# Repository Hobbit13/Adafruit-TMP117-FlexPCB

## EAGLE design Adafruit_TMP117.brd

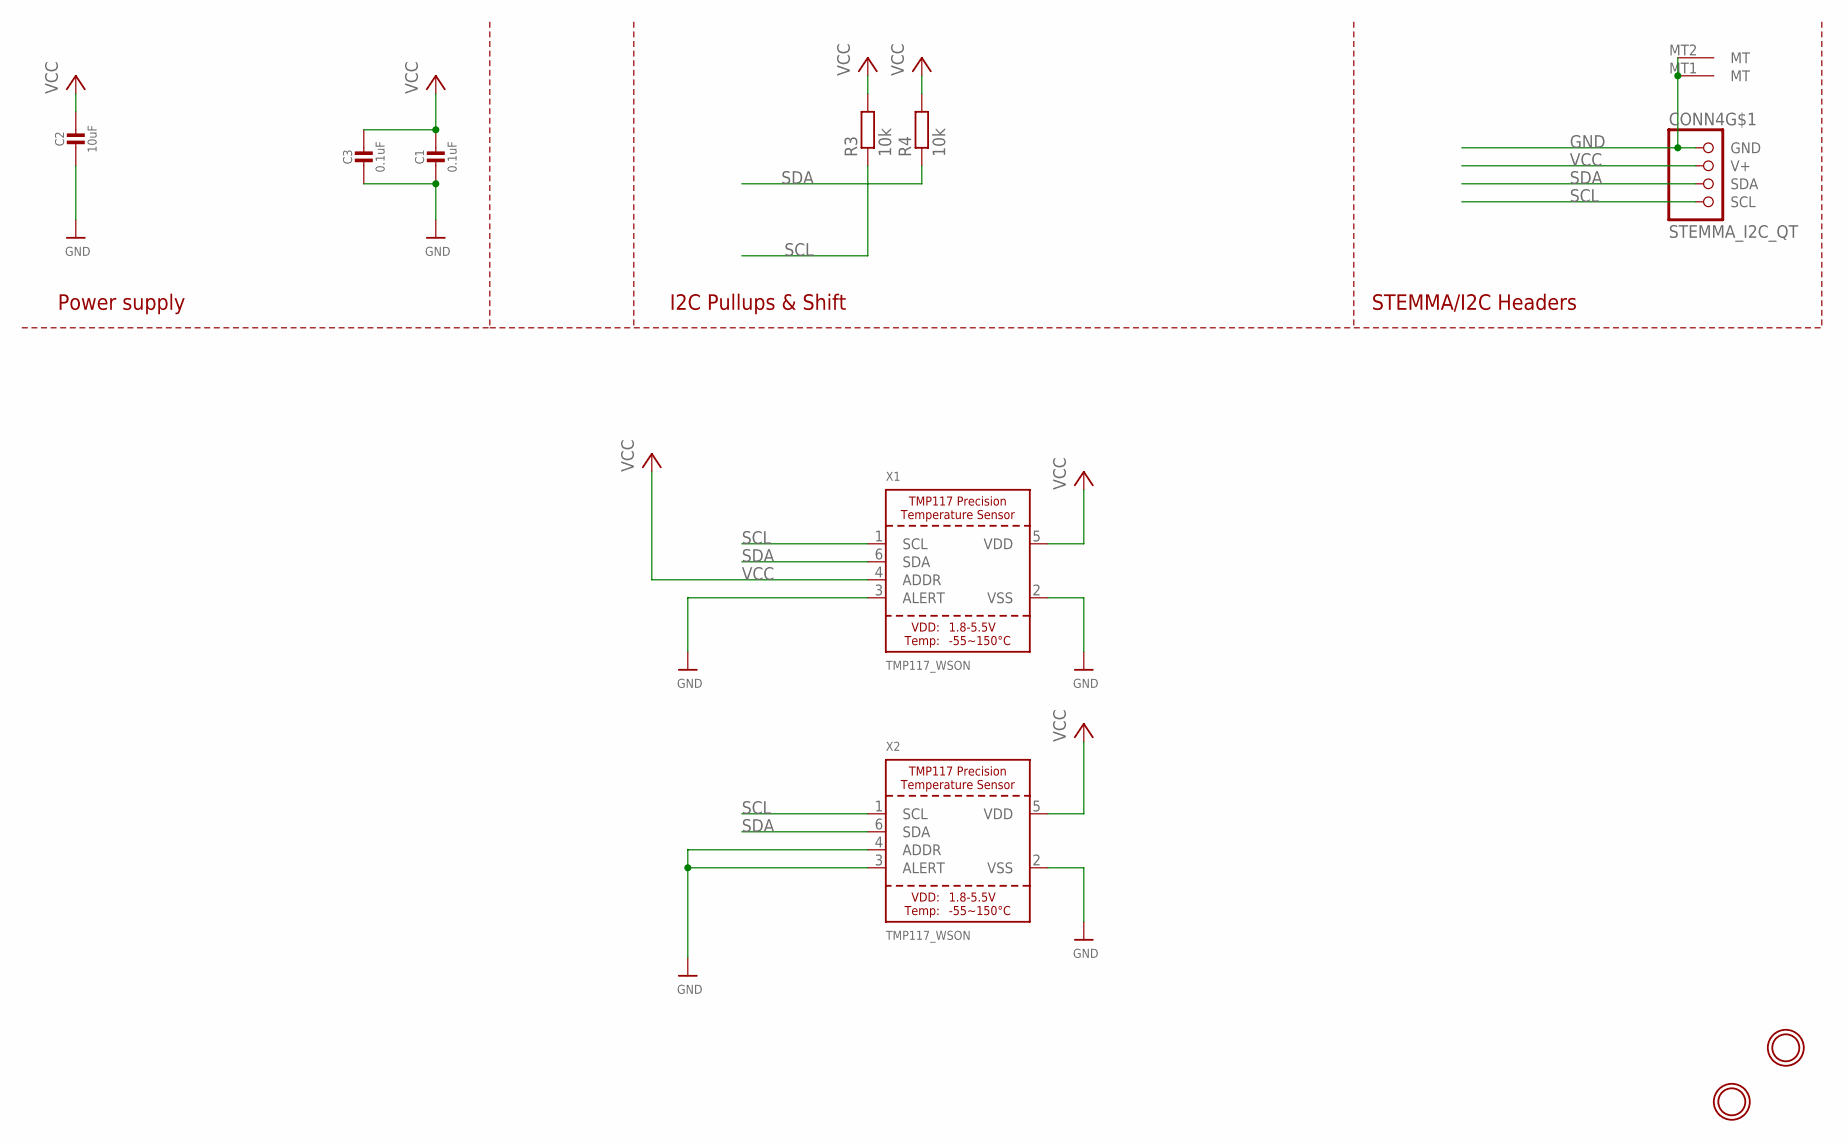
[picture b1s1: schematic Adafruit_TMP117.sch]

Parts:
C1, C3: 0.1uF; _0402
C2: 10uF; _0603
CONN4: STEMMA_I2C_QT; JST_SH4
R3, R4: 10k; R0402
U$1, U$19: MOUNTINGHOLE2.5; MOUNTINGHOLE_2.5_PLATED
X1, X2: TMP117_WSON; WSON-6

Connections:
GND: C1.2, C2.2, C3.2, CONN4.1 (GND), CONN4.MT1 (MT), CONN4.MT2 (MT), X1.2 (VSS), X1.3 (ALERT), X2.2 (VSS), X2.3 (ALERT), X2.4 (ADDR)
SCL: CONN4.4 (SCL), R3.1, X1.1 (SCL), X2.1 (SCL)
SDA: CONN4.3 (SDA), R4.1, X1.6 (SDA), X2.6 (SDA)
VCC: C1.1, C2.1, C3.1, CONN4.2 (V+), R3.2, R4.2, X1.4 (ADDR), X1.5 (VDD), X2.5 (VDD)

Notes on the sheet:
I2C Pullups & Shift
STEMMA/I2C Headers
Power supply

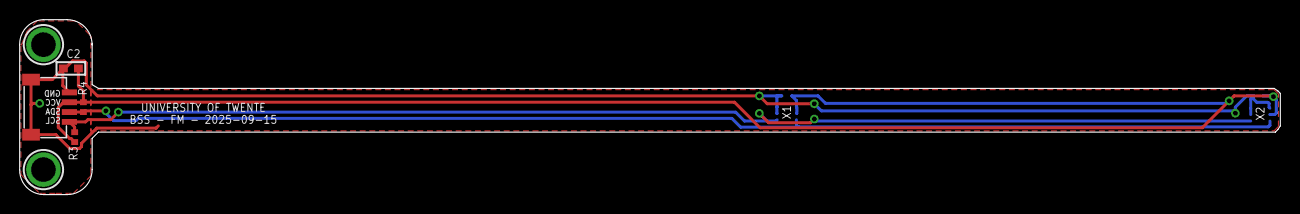
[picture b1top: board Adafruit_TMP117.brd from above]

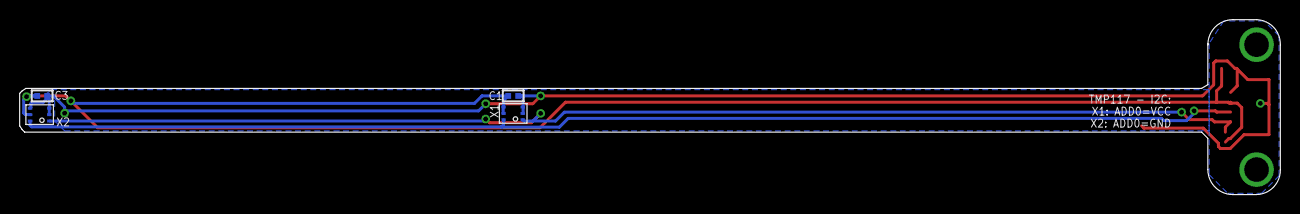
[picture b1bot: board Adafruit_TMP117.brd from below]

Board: 2 copper layers, 128.1 x 17.8 mm, 10 parts (4 on the bottom side), 4 nets.

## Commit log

2025-09-04 changed in to a smaller layout with a "finger" and single connector
2025-09-15 new version, sensors on bottom side, connector on top side. Two sensors with I2C in series.
2025-09-17 added a version with 90deg angle between the two sensors.

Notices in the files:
parts and their libraries:
microbuilder: This work is placed in the public domain, and may be freely used for commercial and non-commercial work with the following conditions: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
